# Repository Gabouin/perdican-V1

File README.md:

<h1 align="center">
  <br>
  
  <br>
  PERDICAN V1
  <br>
</h1>

<h4 align="center">
A STM32 based devboard with an integrated IMU and 14 GPIO pins.
</h4>

<div align="center">

</div>

<p align="center">
  <a href="#about-the-project">About</a> •
  <a href="#repository-structure">Structure</a> •
  <a href="#schematic-on-kicad">Schematic</a> •
  <a href="#pcb-on-kicad">PCB</a> •
  <a href="#bill-of-materials">BOM</a> •
  <a href="#license">License</a> •
  <a href="#contributing">Contributing</a> •
  <a href="#credits">Credits</a>
</p>

<br>
<br>

## About the Project

**PERDICAN** is a STM32 based devboard designed with an integrated IMU, GPIO pins, buttons and LEDs

### Features

- **STM32G431CBT6** MCU 32-Bit 170MHz 128KB (128K x 8) FLASH 48-LQFP (7x7)
- **LSM6DS3TR-C** 6 axis IMU with Accelerometer, Gyroscope, Temperature
- **14 GPIO pins** to help make any hardware project
- **4 debugging pins** with SWCLK, SWDIO, GND and 3V3
- **Status LEDs** to see any error from 5V or 3V3
- **GPIO linked LED** to program it without needing an external LED
- **GPIO linked button** to use it without needing an external button
- **BOOT and RESET buttons**
- **USB-C input**
- **pixelated silkscreen art** to improve the overall look
- **Small size** of 3.7*3.9 cm

## Repository Structure

- `src/kicad/` - KiCad project sources
- `src/kicad/cad/` - full 3d model
- `production/` - PCB fabrication files (Gerbers, BOM, Pick & Place)
- `images/` - images used in the README and documentation

## Schematic on KiCad

Source : `src/kicad/schem/`  

## PCB on KiCad

Source : `src/KiCad/pcb/`  

<div align="center">
  <table>
    <tr>
      <td valign="bottom"></td>
      <td valign="bottom"></td>
      <td valign="bottom"></td>
  </table>
</div>
<div align="center">
  <table>
    <tr>
      <td valign="bottom"></td>
      <td valign="bottom">
</td>
  </table>
</div>  

> The PCB design is made on only 2 layers, to reduce the cost of the board !
<br>

## Build of the Board

<div align="center">
  <table>
    <tr>
      <td valign="center"></td>
      <td valign="center"></td>
    </tr>
  </table>
</div>
<br>

## Bill of Materials

Source: `production/pcb/bom.csv`

|Designator                       |Footprint                       |Quantity|Value           |LCSC Part #|
|---------------------------------|--------------------------------|--------|----------------|-----------|
|3V3, 5V, PA3                     |0603                            |3       |LED             |C2286      |
|BOOT                             |SW-SMD_L3.9-W3.0-P4.45          |1       |BOOT            |C455280    |
|C1, C11, C2, C7, C8              |0603                            |5       |1uF             |C15849     |
|C10, C13, C14, C3, C4, C5, C6, C9|0603                            |8       |100nF           |C14663     |
|C12                              |0603                            |1       |10nF            |C57112     |
|DEBUG                            |PinHeader_1x04_P2.54mm_Vertical |1       |Conn_01x04      |C2691448   |
|IMU1                             |LGA-14_L3.0-W2.5-P0.50-TL       |1       |LSM6DS3TR-C     |C967633    |
|J1                               |PinHeader_1x09_P2.54mm_Vertical |1       |Header Left     |C18213723  |
|J2                               |PinHeader_1x09_P2.54mm_Vertical |1       |Header Right    |C18213723  |
|PA2                              |SW-SMD_L3.9-W3.0-P4.45          |1       |PA2             |C455280    |
|R1, R2                           |0603                            |2       |5.1k            |C23186     |
|R10, R11, R3, R8, R9             |0603                            |5       |10k             |C25804     |
|R4, R5                           |0603                            |2       |100k            |C25803     |
|R6, R7                           |0603                            |2       |4.7k            |C23162     |
|RESET                            |SW-SMD_L3.9-W3.0-P4.45          |1       |RESET           |C455280    |
|STM32                            |LQFP-48_L7.0-W7.0-P0.50-LS9.0-BL|1       |STM32G431CBT6   |C529355    |
|U1                               |SOT-23-3                        |1       |XC6206PxxxMR    |C5446      |
|USB-C1                           |USB-C-SMD_TYPE-C-16PIN-2MD-073  |1       |TYPE-C 16PIN 2MD|C2765186   |

## JLPCB order

### LCSC parts 

<div align="center">
  <table>
    <tr>
      <td valign="bottom"></td>
      <td valign="bottom"></td>
  </table>
</div>  

>The PCB is expensive due to small vias. This will be arranged with bigger vias for the V2. BTW, I am not ordering it, I will do so for the V2.
<br>

## You might also like

- [APX USB HUB](https://github.com/gabouin/APX-USB-HUB) - A PTC-secured USB HUB designed for [Macondo - Hack Club](https://macondo.hackclub.com)
- [HackPad](https://github.com/Gabouin/Hackpad) - A 6-keys macropad designed for [Blueprint - Hack Club](https://blueprint.hackclub.com)
- See more in my [github](https://github.com/gabouin)

## Contributing

Contributions, improvements, and remixes are welcome! Please read the [CONTRIBUTING.md](CONTRIBUTING.md) guide to get started.

## License

This project is licensed under the **MIT License** - see the [LICENSE](LICENSE) file for details.

## Credits

This project uses:

- **KiCad** - PCB design and schematic capture
- **JLCPCB** - PCB manufacturing
- **LCSC** - Parts order
- **Figma** - Silkscreen and banner design
- **Blender** - CAD render
- **[@NotARoomba](https://github.com/notaroomba)** - Readme template

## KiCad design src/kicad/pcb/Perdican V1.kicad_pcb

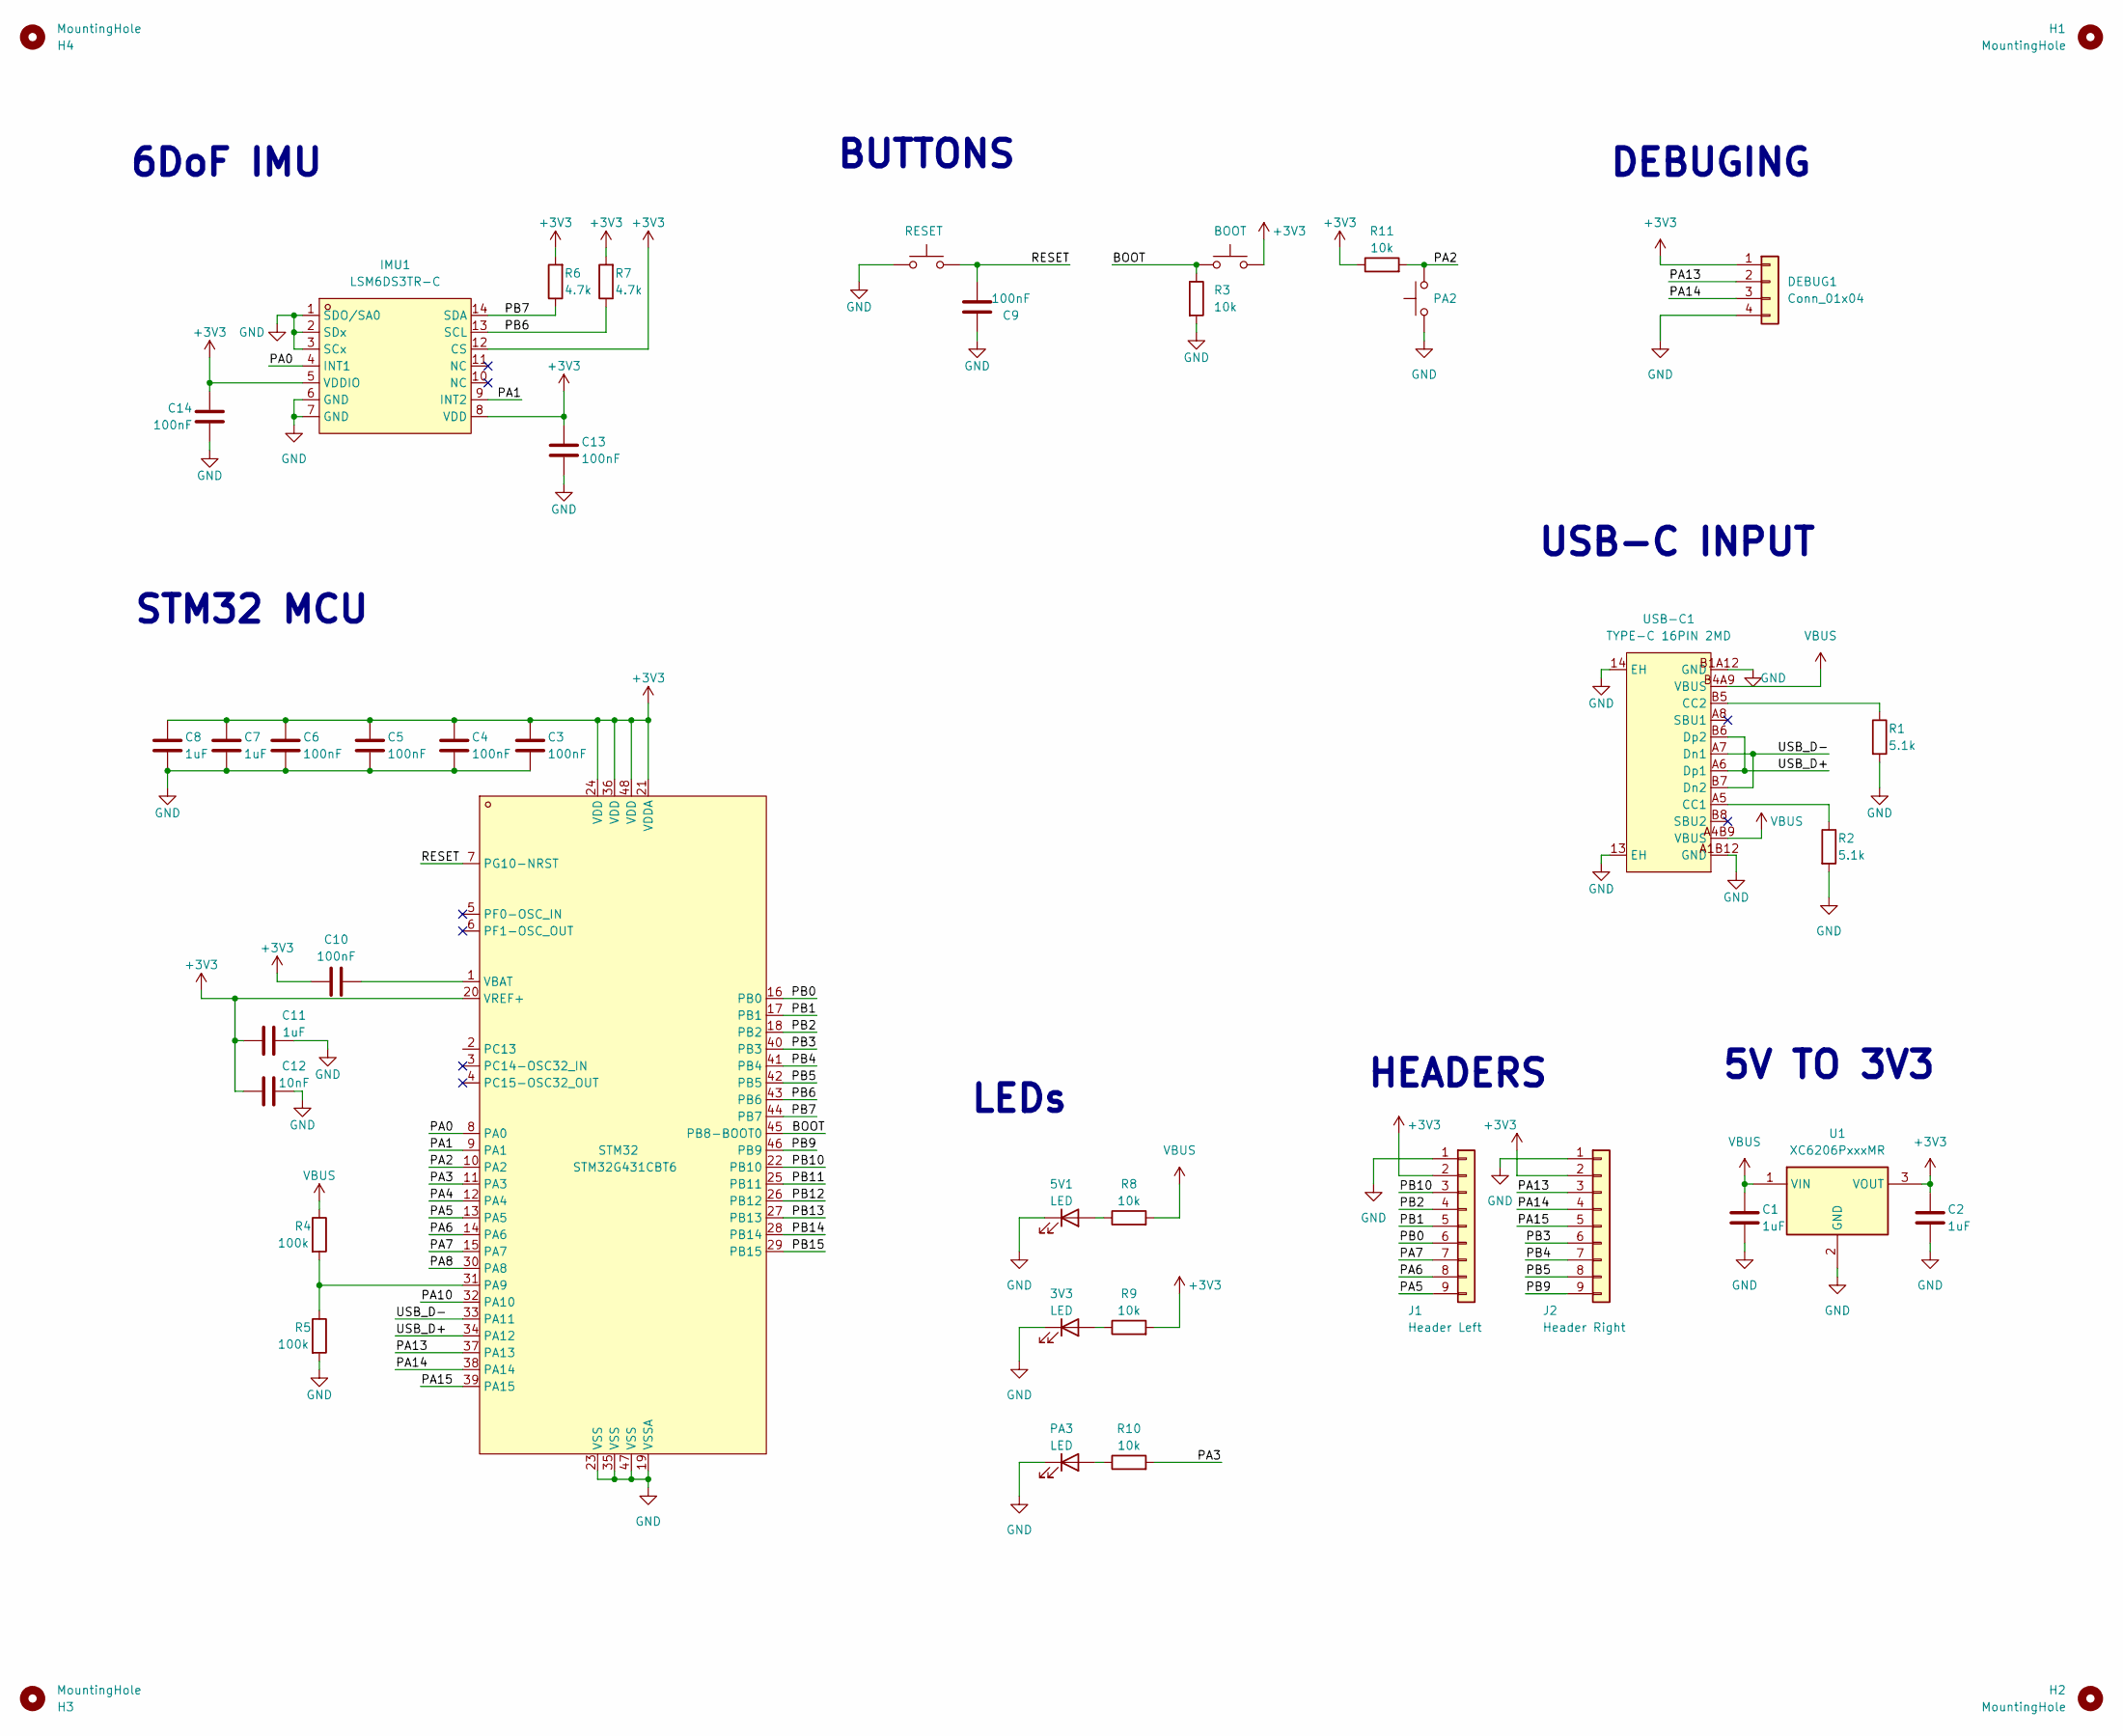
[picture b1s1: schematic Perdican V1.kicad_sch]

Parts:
3V3, 5V1: LED; LED_0603_1608Metric
BOOT1: BOOT; SW-SMD_L3.9-W3.0-P4.45
C1, C2, C7, C8, C11: 1uF; C_0603_1608Metric
C3, C4, C5, C6, C9, C10, C13, C14: 100nF; C_0603_1608Metric
C12: 10nF; C_0603_1608Metric
DEBUG1: Conn_01x04; PinHeader_1x04_P2.54mm_Vertical
H1, H2, H3, H4: MountingHole; MountingHole_2.2mm_M2
IMU1: LSM6DS3TR-C; LGA-14_L3.0-W2.5-P0.50-TL; MPN LSM6DS3TR-C; LCSC Part C967633
J1: Header Left; PinHeader_1x09_P2.54mm_Vertical
J2: Header Right; PinHeader_1x09_P2.54mm_Vertical
PA2: PA2; SW-SMD_L3.9-W3.0-P4.45
PA3: LED; LED_0603_1608Metric
R1, R2: 5.1k; R_0603_1608Metric
R3, R8, R9, R10, R11: 10k; R_0603_1608Metric
R4, R5: 100k; R_0603_1608Metric
R6, R7: 4.7k; R_0603_1608Metric
RESET1: RESET; SW-SMD_L3.9-W3.0-P4.45
STM32: STM32G431CBT6; LQFP-48_L7.0-W7.0-P0.50-LS9.0-BL; MPN STM32G431CBT6; LCSC Part C529355
U1: XC6206PxxxMR; SOT-23-3
USB-C1: TYPE-C 16PIN 2MD; USB-C-SMD_TYPE-C-16PIN-2MD-073; MPN TYPE-C 16PIN 2MD(073); LCSC Part C2765186

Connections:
+3V3: BOOT1.2, C2.1, C3.1, C4.1, C5.1, C6.1, C7.1, C8.1, C10.1, C11.1, C12.1, C13.1, C14.1, DEBUG1.1, IMU1.5 (VDDIO), IMU1.8 (VDD), IMU1.12 (CS), J1.2, J2.2, R6.2, R7.2, R9.2, R11.1, STM32.20 (VREF+), STM32.21 (VDDA), STM32.24 (VDD), STM32.36 (VDD), STM32.48 (VDD), U1.3 (VOUT); also elsewhere on the board
/BOOT: BOOT1.1, R3.1, STM32.45 (PB8-BOOT0); also elsewhere on the board
/PA0: IMU1.4 (INT1), STM32.8 (PA0)
/PA1: IMU1.9 (INT2), STM32.9 (PA1)
/PA2: PA2.2, R11.2, STM32.10 (PA2)
/PA3: R10.2, STM32.11 (PA3)
/PA4: STM32.12 (PA4)
/PA5: J1.9, STM32.13 (PA5)
/PA6: J1.8, STM32.14 (PA6)
/PA7: J1.7, STM32.15 (PA7)
/PA8: STM32.30 (PA8)
/PA10: STM32.32 (PA10)
/PA13: DEBUG1.2, J2.3, STM32.37 (PA13); also elsewhere on the board
/PA14: DEBUG1.3, J2.4, STM32.38 (PA14); also elsewhere on the board
/PA15: J2.5, STM32.39 (PA15)
/PB0: J1.6, STM32.16 (PB0)
/PB1: J1.5, STM32.17 (PB1)
/PB2: J1.4, STM32.18 (PB2)
/PB3: J2.6, STM32.40 (PB3)
/PB4: J2.7, STM32.41 (PB4)
/PB5: J2.8, STM32.42 (PB5)
/PB6: IMU1.13 (SCL), R7.1, STM32.43 (PB6)
/PB7: IMU1.14 (SDA), R6.1, STM32.44 (PB7)
/PB9: J2.9, STM32.46 (PB9)
/PB10: J1.3, STM32.22 (PB10)
/PB11: STM32.25 (PB11)
/PB12: STM32.26 (PB12)
/PB13: STM32.27 (PB13)
/PB14: STM32.28 (PB14)
/RESET: C9.2, RESET1.2, STM32.7 (PG10-NRST); also elsewhere on the board
/USB_D+: STM32.34 (PA12), USB-C1.A6 (Dp1), USB-C1.B6 (Dp2)
/USB_D-: STM32.33 (PA11), USB-C1.A7 (Dn1), USB-C1.B7 (Dn2)
GND: 3V3.1 (K), 5V1.1 (K), C1.2, C2.2, C3.2, C4.2, C5.2, C6.2, C7.2, C8.2, C9.1, C11.2, C12.2, C13.2, C14.2, DEBUG1.4, IMU1.1 (SDO/SA0), IMU1.2 (SDx), IMU1.3 (SCx), IMU1.6 (GND), IMU1.7 (GND), J1.1, J2.1, PA2.1, PA3.1 (K), R1.2, R2.2, R3.2, R5.2, RESET1.1, STM32.19 (VSSA), STM32.23 (VSS), STM32.35 (VSS), STM32.47 (VSS), U1.2 (GND), USB-C1.13 (EH), USB-C1.14 (EH), USB-C1.A1B12 (GND), USB-C1.B1A12 (GND); also elsewhere on the board
unnamed: 3V3.2 (A), R9.1
unnamed 34: 5V1.2 (A), R8.1; also elsewhere on the board
unnamed: PA3.2 (A), R10.1
unnamed: R4.2, R5.1, STM32.31 (PA9)
unnamed: C10.2, STM32.1 (VBAT)
unnamed: R2.1, USB-C1.A5 (CC1)
unnamed: R1.1, USB-C1.B5 (CC2)
VBUS: C1.1, R4.1, R8.2, U1.1 (VIN), USB-C1.A4B9 (VBUS), USB-C1.B4A9 (VBUS)

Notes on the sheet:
LEDs
BUTTONS
6DoF IMU
USB-C INPUT
STM32 MCU
HEADERS
DEBUGING
5V TO 3V3

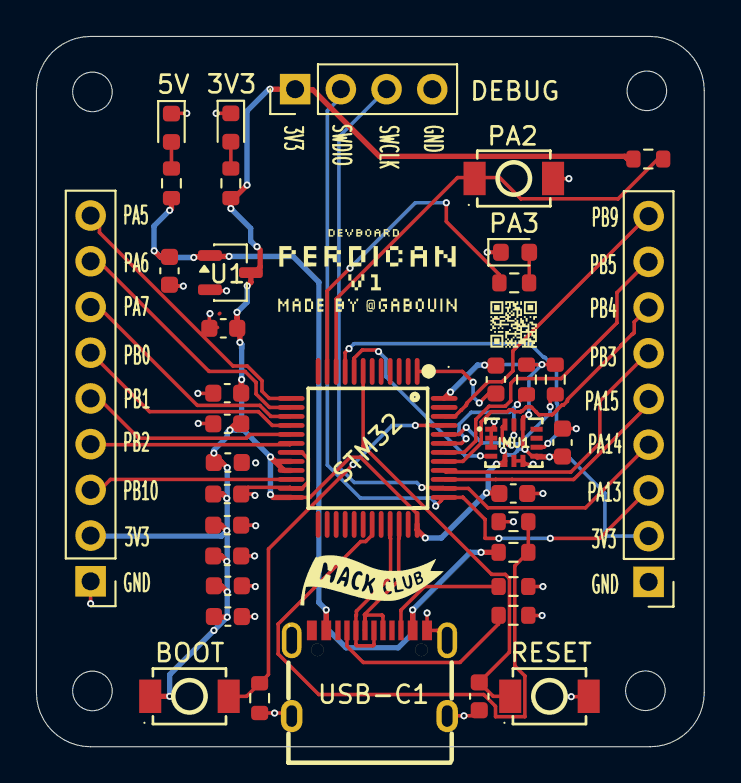
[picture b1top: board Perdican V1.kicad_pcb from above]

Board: 2 copper layers, 37.1 x 39.5 mm, 42 parts (0 on the bottom side), 34 nets.

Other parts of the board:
5V: LED; LED_0603_1608Metric
BOOT: BOOT; SW-SMD_L3.9-W3.0-P4.45
DEBUG: Conn_01x04; PinHeader_1x04_P2.54mm_Vertical
RESET: RESET; SW-SMD_L3.9-W3.0-P4.45

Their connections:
+3V3: BOOT.2, DEBUG.1; also elsewhere on the board
/BOOT: BOOT.1; also elsewhere on the board
/PA13: DEBUG.2; also elsewhere on the board
/PA14: DEBUG.3; also elsewhere on the board
/RESET: RESET.2; also elsewhere on the board
GND: 5V.1 (K), DEBUG.4, RESET.1; also elsewhere on the board
unnamed 34: 5V.2 (A); also elsewhere on the board

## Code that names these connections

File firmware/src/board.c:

#include "board.h"
#include "gpio.h"
#include "clock.h"
#include "systick.h"
#include <strings.h>

const board_gpio_t board_gpios[BOARD_GPIO_COUNT] = {
    { "PB10", GPIOB, 10u, 1u, 3u },
    { "PB2",  GPIOB,  2u, 1u, 4u },
    { "PB1",  GPIOB,  1u, 1u, 5u },
    { "PB0",  GPIOB,  0u, 1u, 6u },
    { "PA7",  GPIOA,  7u, 1u, 7u },
    { "PA6",  GPIOA,  6u, 1u, 8u },
    { "PA5",  GPIOA,  5u, 1u, 9u },
    { "PA13", GPIOA, 13u, 2u, 3u },
    { "PA14", GPIOA, 14u, 2u, 4u },
    { "PA15", GPIOA, 15u, 2u, 5u },
    { "PB3",  GPIOB,  3u, 2u, 6u },
    { "PB4",  GPIOB,  4u, 2u, 7u },
    { "PB5",  GPIOB,  5u, 2u, 8u },
    { "PB9",  GPIOB,  9u, 2u, 9u },
};

const board_gpio_t *board_gpio_find(const char *name)
{
    for (unsigned i = 0; i < BOARD_GPIO_COUNT; i++)
        if (strcasecmp(name, board_gpios[i].name) == 0)
            return &board_gpios[i];
    return 0;
}

bool board_pin_is_swd(GPIO_TypeDef *port, uint8_t pin)
{
    return port == GPIOA && (pin == SWDIO_PIN || pin == SWCLK_PIN);
}

void led_set(bool on)
{
#if LED_ACTIVE_HIGH
    gpio_write(LED_PORT, LED_PIN, on);
#else
    gpio_write(LED_PORT, LED_PIN, !on);
#endif
}

void led_toggle(void)
{
    gpio_toggle(LED_PORT, LED_PIN);
}

bool led_get(void)
{
    bool level = gpio_read_output(LED_PORT, LED_PIN);
#if LED_ACTIVE_HIGH
    return level;
#else
    return !level;
#endif
}

#define BTN_DEBOUNCE_MS 20u

static volatile bool     s_btn_stable;
static volatile bool     s_btn_press_edge;
static bool              s_btn_last_raw;
static uint32_t          s_btn_last_change;

bool button_raw(void)
{
    bool level = gpio_read(BTN_PORT, BTN_PIN);
#if BTN_ACTIVE_LOW
    return !level;
#else
    return level;
#endif
}

bool button_pressed(void)
{
    return s_btn_stable;
}

bool button_take_press(void)
{
    if (!s_btn_press_edge)
        return false;
    s_btn_press_edge = false;
    return true;
}

void board_poll_button(uint32_t now_ms)
{
    bool raw = button_raw();

    if (raw != s_btn_last_raw) {
        s_btn_last_raw    = raw;
        s_btn_last_change = now_ms;
        return;
    }

    if ((now_ms - s_btn_last_change) < BTN_DEBOUNCE_MS)
        return;

    if (raw != s_btn_stable) {
        s_btn_stable = raw;
        if (raw)
            s_btn_press_edge = true;
    }
}

bool vbus_present(void)
{
    return gpio_read(VBUS_PORT, VBUS_PIN);
}

static void park_unused_pins(void)
{
    static const uint8_t pa_unused[] = { 4u, 8u, 10u };
    static const uint8_t pb_unused[] = { 11u, 12u, 13u, 14u, 15u };
    static const uint8_t pc_unused[] = { 13u, 14u, 15u };
    static const uint8_t pf_unused[] = { 0u, 1u };

    for (unsigned i = 0; i < sizeof pa_unused; i++)
        gpio_config_analog(GPIOA, pa_unused[i]);
    for (unsigned i = 0; i < sizeof pb_unused; i++)
        gpio_config_analog(GPIOB, pb_unused[i]);
    for (unsigned i = 0; i < sizeof pc_unused; i++)
        gpio_config_analog(GPIOC, pc_unused[i]);
    for (unsigned i = 0; i < sizeof pf_unused; i++)
        gpio_config_analog(GPIOF, pf_unused[i]);
}

void board_init(void)
{
    clock_init();
    clock_init_periph();
    systick_init();

    led_set(false);
    gpio_config_output(LED_PORT, LED_PIN, GPIO_PP, GPIO_SPEED_LOW);
    led_set(false);

    gpio_config_input(BTN_PORT, BTN_PIN, GPIO_PULL_UP);

    gpio_config_input(VBUS_PORT, VBUS_PIN, GPIO_PULL_NONE);

    gpio_config_input(IMU_INT1_PORT, IMU_INT1_PIN, GPIO_PULL_DOWN);
    gpio_config_input(IMU_INT2_PORT, IMU_INT2_PIN, GPIO_PULL_DOWN);

    gpio_config_input(BOOT0_PORT, BOOT0_PIN, GPIO_PULL_NONE);

    park_unused_pins();
}

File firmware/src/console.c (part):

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        "  id                   board, clock and chip identity\r\n"
        "  uptime               milliseconds since boot\r\n"
        "\r\n"
        "  led on|off|toggle    drive the user LED (PA3)\r\n"
        "  btn                  read the user button (PA2)\r\n"
        "  vbus                 USB bus power present (PA9)\r\n"
        "\r\n"
        "  imu                  one accel/gyro/temp reading\r\n"
        "  imu stream [hz]      stream readings, any key stops\r\n"
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        "  i2cscan              probe every address on I2C1\r\n"
        "\r\n"
        "  pins                 expansion header map\r\n"
        "  gpio <pin> read      read a header pin (e.g. gpio PB0 read)\r\n"
        "  gpio <pin> out 0|1   drive a header pin\r\n"
        "  gpio <pin> in [pu|pd]  make a header pin an input\r\n"
        "\r\n"
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    printf("sysclk   : %lu Hz (HSI16 -> PLL, no crystal fitted)\r\n",
           (unsigned long)BOARD_SYSCLK_HZ);
    printf("usb clk  : HSI48 + CRS locked to host SOF\r\n");
    printf("i2c1     : PB6/PB7 @ 400 kHz, clocked from HSI16\r\n");
    printf("imu      : LSM6DS3TR-C at 7-bit 0x%02X (SA0 grounded)\r\n", IMU_I2C_ADDR7);
    printf("vbus     : %s\r\n", vbus_present() ? "present" : "absent");
}
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
static void cmd_i2cscan(void)
{
    cdc_puts("scanning I2C1 (PB6/PB7)...\r\n");

    unsigned found = 0;
    for (uint8_t a = 0x08u; a <= 0x77u; a++) {
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               l->position, l->name, r->position, r->name, note);
    }

    cdc_puts("\r\non-board: PA3 LED (active high), PA2 button (active low),\r\n");
    cdc_puts("          PB6/PB7 IMU I2C, PA0/PA1 IMU INT1/INT2,\r\n");
    cdc_puts("          PA9 VBUS sense, PB8 BOOT0, PA11/PA12 USB\r\n");
    cdc_puts("DEBUG hdr: 1 +3V3, 2 SWDIO, 3 SWCLK, 4 GND\r\n");
}

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
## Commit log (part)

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2026-05-11 Add BOM CSV file for PCB components
2026-05-11 Revise README for improved presentation and content
    Updated README.md with enhanced formatting and additional project details.
2026-05-11 Update project name from APX USB HUB to PERDICAN V1
2026-05-11 Add MIT License to the project
2026-05-11 change folder of kicad pro
2026-05-11 Rename src/kicad/Perdican V1.kicad_pcb to src/kicad/pcb/Perdican V1.kicad_pcb
2026-05-11 Rename src/kicad/Perdican V1.kicad_sch to src/kicad/schem/Perdican V1.kicad_sch
2026-05-11 Rename src/kicad/Perdican V1.step to src/kicad/cad/Perdican V1.step
2026-05-11 Add PERDICAN_bom.csv to production/pcb directory
2026-05-11 Create images
2026-05-11 Rename Capture d'écran 2026-05-11 175846.png to images/banner
2026-05-11 add images
2026-05-11 Rename Capture d'écran 2026-05-11 160712.png to typologoP
2026-05-11 Rename typologoP to typologoP.png
2026-05-11 Rename banner to banner.png

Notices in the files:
README.md:
License: MIT
